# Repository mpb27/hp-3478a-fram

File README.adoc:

= hp-3478a-fram

Yet another HP 3478A calibration RAM replacement using FRAM.

[WARNING]
====
[.big]#*UNTESTED*#

The schematic, layout, and BOM are complete, but the PCB has not been verified to work.

*Status:* Awaiting PCB delivery and sourcing of parts.
====

== Main changes

* One resistor value (10kΩ) and one capacitor value (0.1μF) - both 0603.
* One gate IC - *74LVC1G58* for all logic - SOT-23-6.
* Smaller size (0.70" x 1.15").
* Voltage supervisor changed to *xxx**803*** variants with ~4V cutoff.

== Notes

* For 0.1" DIP SMT pins, match the pin plating (gold/tin) to the socket plating. Plating does not matter if soldering directly.
* The µPD5105L RAM uses a 0.4" DIP width. Choose an appropriately sized socket if using one.
* The 803 voltage supervisors are available in multiple pinout configurations. Carefully verify the pinout when selecting alternatives not listed.

== Ordering
* US / Canada: OSHPark https://oshpark.com/shared_projects/5y6FeQE9[Order Link]
* China: JLCPCB https://jlcpcb.com/quote[Upload Gerbers from release folder]

== Future Work
* Verify the PCB works as expected.
* Increase resistor values to 47kΩ -- the 10kΩ resistors are overkill.
* Add OSHW license and attribution.

== Design

=== Schematic (Rev1)

image::README.assets/image-20260909163049997.png[]

=== PCB (Rev1)

[cols="a,a", frame=none, grid=none]
|===
| image::README.assets/image-20260909163140836.png[width=300]
| image::README.assets/image-20260909163228986.png[width=300]
|===

=== BOM (Rev1)

[cols="1,2,1,2,4,3,3,3",options="header"]
|===
| # | Reference | Qty | Value | Description | Manufacturer | MPN | Alternate PN

| 1
| C1,C2
| 2
| 0.1u
| CAP CER 0.1UF 50V X7R 0603
| Murata Electronics
| GCM188L81H104
| KGM15BR71H104KT

| 2
| J1,J2
| 1
| M20-8771146
| CONN HEADER SMD 11POS 2.54MM
| Harwin Inc
| M20-8771146
| PZ254VS-11-11P

| 3
| R1,R2,R3,R4,R5,R6
| 6
| 10k
| RES 10K OHM 1% 1/10W 0603
| Vishay Dale
| CRCW060310K0FKEA
| RK73H1JTTD1002F

| 4
| SW1
| 1
| CHS-02TB
| SWITCH SLIDE DIP SPST 0.1A 6V
| Nidec Components
| CHS-02TB
| DHA-02NTQR

| 5
| U1
| 1
| FM16W08-SG
| IC FRAM 64KBIT PARALLEL 28-SOIC
| Infineon Technologies
| FM16W08-SG
| N/A

| 6
| U2,U3,U4,U5,U6
| 5
| 74LVC1G58W6
| IC MF/CFG 1-CIR 3-IN SOT-23-6
| Diodes Inc
| 74LVC1G58W6-7
| SN74LVC1G58DBV

| 7
| U7
| 1
| APX803L20-41SA
| IC SUPERVISOR 1CH 4.0V SOT-23
| Diodes Inc
| APX803L20-41SA
| MIC803-40D3VM3
|===

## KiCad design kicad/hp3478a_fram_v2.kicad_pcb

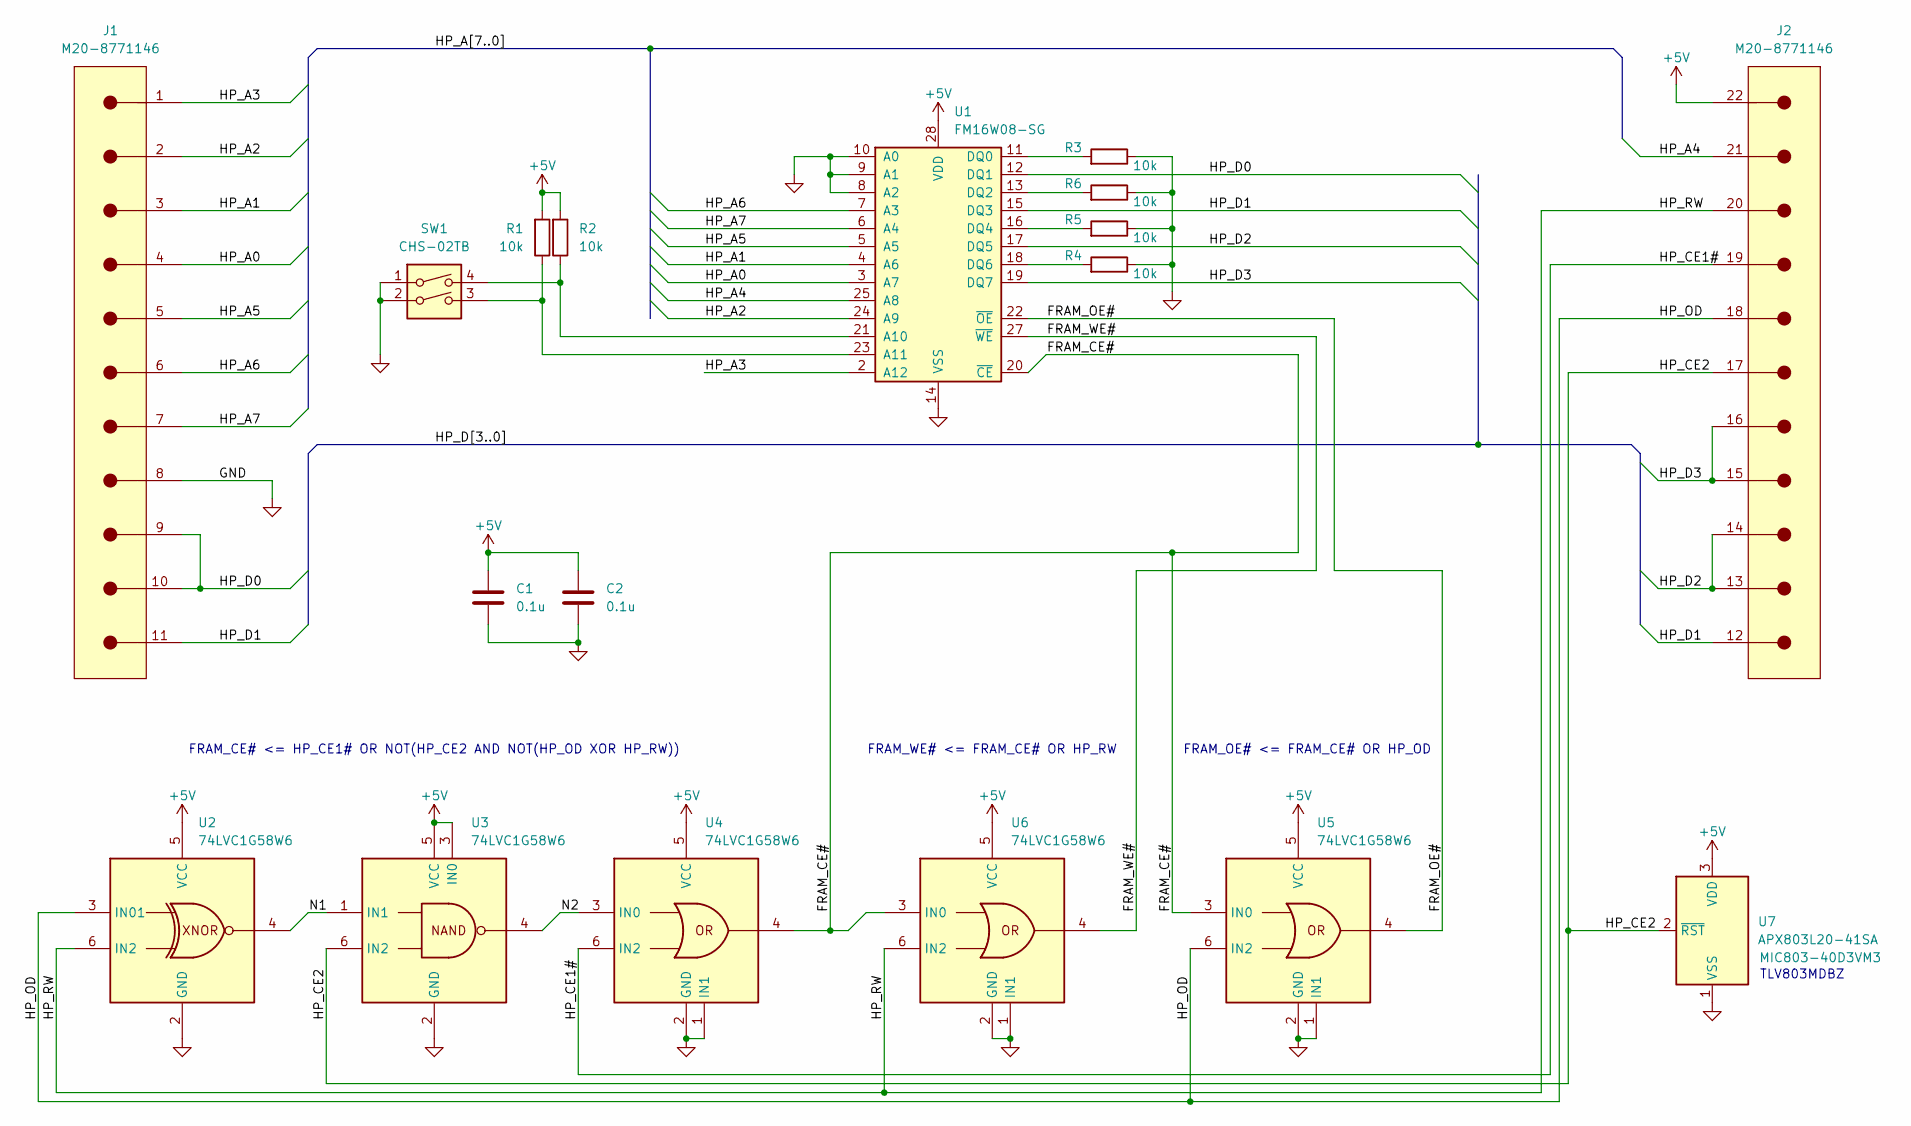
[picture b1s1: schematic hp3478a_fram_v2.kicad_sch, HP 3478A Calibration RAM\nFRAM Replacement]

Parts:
C1, C2: 0.1u; C_0603_1608Metric; MPN GCM188L81H104
J1: M20-8771146; PinHeader_1x11_P2.54mm_Vertical_SMD_Pins_1_11; MPN M20-8771146
J2: M20-8771146; PinHeader_1x11_P2.54mm_Vertical_SMD_Pins_12_22; MPN M20-8771146
R1, R2, R3, R4, R5, R6: 10k; R_0603_1608Metric; MPN CRCW060310K0FKEA
SW1: CHS-02TB; SW_DIP_SPSTx02_Slide_Copal_CHS-02B_W7.62mm_P1.27mm; MPN CHS-02TB
U1: FM16W08-SG; SOIC-28W_7.5x17.9mm_P1.27mm; MPN FM16W08-SG
U2, U3, U4, U5, U6: 74LVC1G58W6; SOT-23-6; MPN 74LVC1G58W6-7
U7: APX803L20-41SA; SOT-23; MPN APX803L20-41SA

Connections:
+5V: C1.1, C2.1, J2.22, R1.1, R2.1, U1.28 (VDD), U2.5 (VCC), U3.3 (IN0), U3.5 (VCC), U4.5 (VCC), U5.5 (VCC), U6.5 (VCC), U7.3 (VDD)
/FRAM_CE#: U1.20 (~CE), U4.4, U5.3 (IN0), U6.3 (IN0)
/FRAM_OE#: U1.22 (~OE), U5.4
/FRAM_WE#: U1.27 (~WE), U6.4
/HP_A0: J1.4, U1.3 (A7)
/HP_A1: J1.3, U1.4 (A6)
/HP_A2: J1.2, U1.24 (A9)
/HP_A3: J1.1, U1.2 (A12)
/HP_A4: J2.21, U1.25 (A8)
/HP_A5: J1.5, U1.5 (A5)
/HP_A6: J1.6, U1.7 (A3)
/HP_A7: J1.7, U1.6 (A4)
/HP_CE1#: J2.19, U4.6 (IN2)
/HP_CE2: J2.17, U3.6 (IN2), U7.2 (~RST)
/HP_D0: J1.9, J1.10, U1.12 (DQ1)
/HP_D1: J1.11, J2.12, U1.15 (DQ3)
/HP_D2: J2.13, J2.14, U1.17 (DQ5)
/HP_D3: J2.15, J2.16, U1.19 (DQ7)
/HP_OD: J2.18, U2.1 (IN1), U2.3 (IN01), U5.6 (IN2)
/HP_RW: J2.20, U2.6 (IN2), U6.6 (IN2)
/N1: U2.4, U3.1 (IN1)
/N2: U3.4, U4.3 (IN0)
GND: C1.2, C2.2, J1.8, R3.2, R4.2, R5.2, R6.2, SW1.1, SW1.2, U1.8 (A2), U1.9 (A1), U1.10 (A0), U1.14 (VSS), U2.2 (GND), U3.2 (GND), U4.1 (IN1), U4.2 (GND), U5.1 (IN1), U5.2 (GND), U6.1 (IN1), U6.2 (GND), U7.1 (VSS)
unnamed: R2.2, SW1.4, U1.21 (A10)
unnamed: R1.2, SW1.3, U1.23 (A11)
unnamed: R3.1, U1.11 (DQ0)
unnamed: R6.1, U1.13 (DQ2)
unnamed: R5.1, U1.16 (DQ4)
unnamed: R4.1, U1.18 (DQ6)

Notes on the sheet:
TLV803MDBZ
FRAM_CE# <= HP_CE1# OR NOT(HP_CE2 AND NOT(HP_OD XOR HP_RW))
FRAM_WE# <= FRAM_CE# OR HP_RW
FRAM_OE# <= FRAM_CE# OR HP_OD

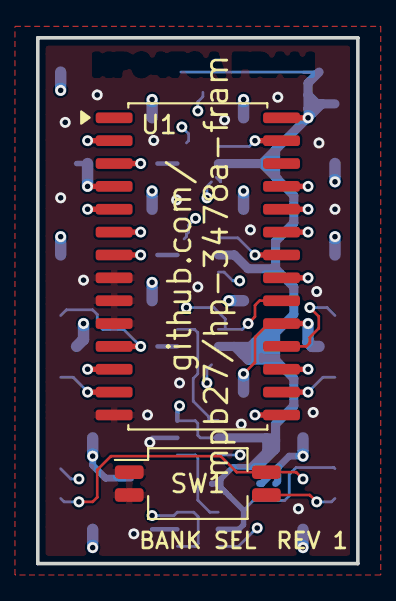
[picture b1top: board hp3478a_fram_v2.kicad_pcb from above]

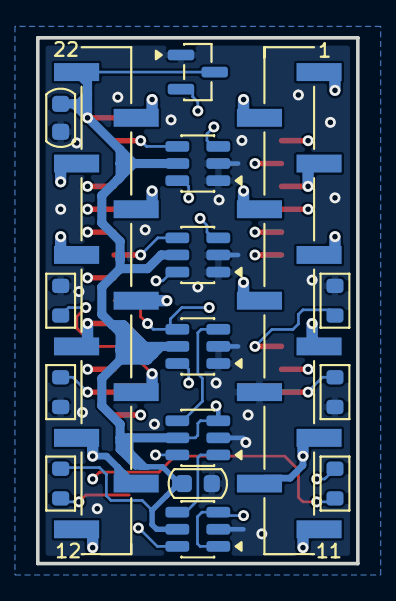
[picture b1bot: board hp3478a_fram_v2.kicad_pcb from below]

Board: 4 copper layers, 17.8 x 29.2 mm, 18 parts (16 on the bottom side), 29 nets.
